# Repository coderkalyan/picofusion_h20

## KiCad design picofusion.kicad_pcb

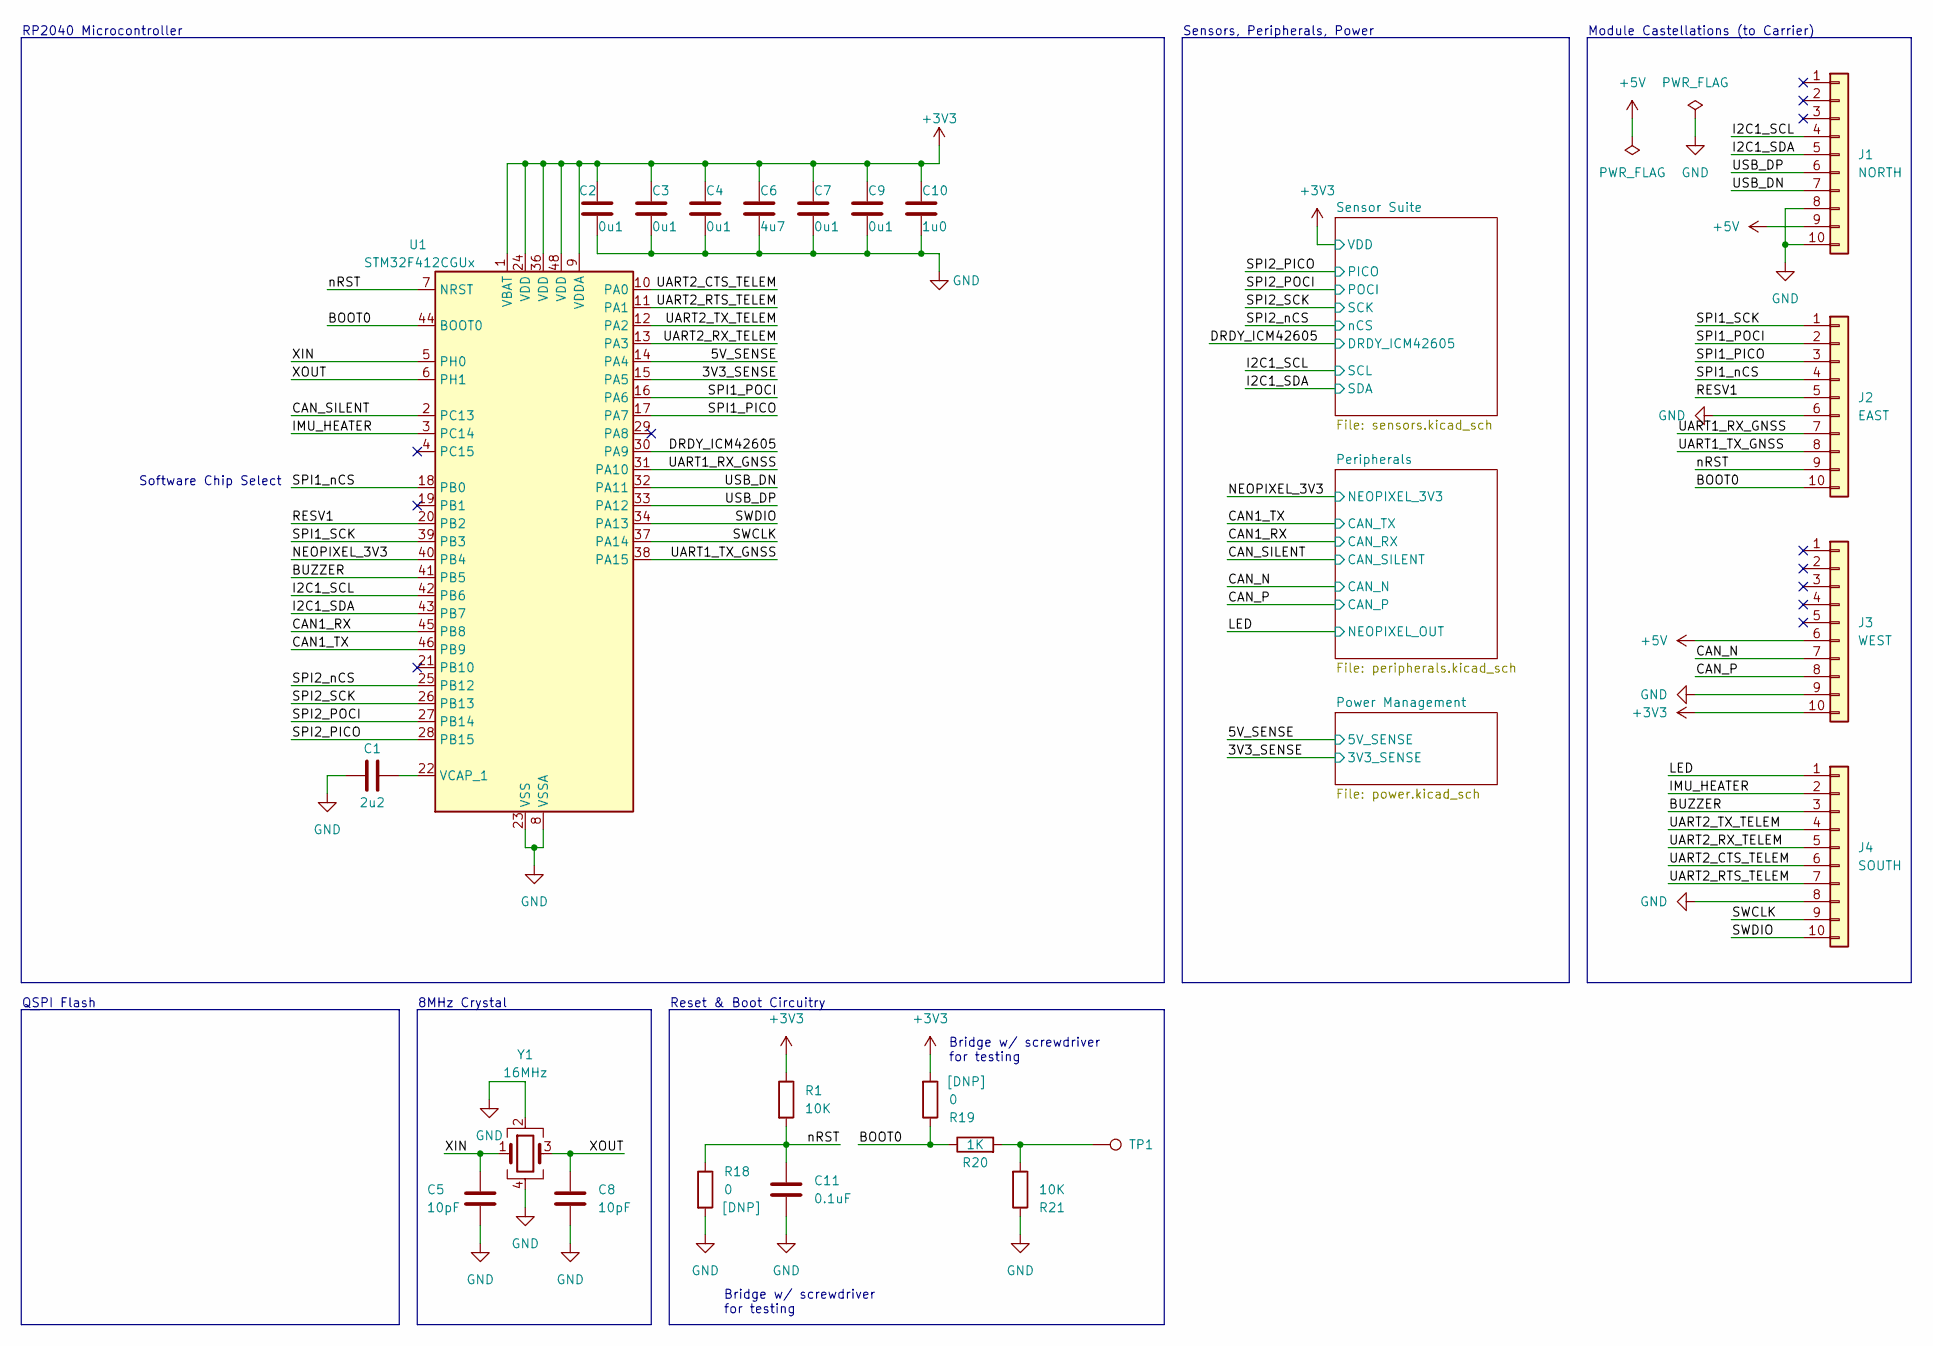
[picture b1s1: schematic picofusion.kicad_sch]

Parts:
C1: 2u2; C_0201_0603Metric
C2, C3, C4, C7, C9: 0u1; C_0201_0603Metric
C5, C8: 10pF; C_0402_1005Metric
C6: 4u7; C_0201_0603Metric
C10: 1u0; C_0201_0603Metric
C11: 0.1uF; C_0201_0603Metric
J1: NORTH; PinCastellation_1x10_P2.00mm_Vertical
J2: EAST; PinCastellation_1x10_P2.00mm_Vertical
J3: WEST; PinCastellation_1x10_P2.00mm_Vertical
J4: SOUTH; PinCastellation_1x10_P2.00mm_Vertical
R1: 10K; R_0201_0603Metric
R18, R19: 0; TestPoint_2Pin_0402_1005Metric
R20: 1K; R_0201_0603Metric
R21: 10K; R_0402_1005Metric
TP1: TestPoint; TestPoint_Pad_1.0x1.0mm
U1: STM32F412CGUx; QFN-48-1EP_7x7mm_P0.5mm_EP5.6x5.6mm
Y1: 16MHz; Crystal_SMD_2016-4Pin_2.0x1.6mm; Part R2520-12.000-10-3030-TR

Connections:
+3V3: C2.1, C3.1, C4.1, C6.1, C7.1, C9.1, C10.1, J3.10, R1.1, R19.2, U1.1 (VBAT), U1.9 (VDDA), U1.24 (VDD), U1.36 (VDD), U1.48 (VDD); also elsewhere on the board
+5V: J1.9, J3.6; also elsewhere on the board
/3V3_SENSE: U1.15 (PA5); also elsewhere on the board
/5V_SENSE: U1.14 (PA4); also elsewhere on the board
/BOOT0: J2.10, R19.1, R20.1, U1.44 (BOOT0)
/BUZZER: J4.3, U1.41 (PB5)
/CAN1_RX: U1.45 (PB8); also elsewhere on the board
/CAN1_TX: U1.46 (PB9); also elsewhere on the board
/CAN_N: J3.7; also elsewhere on the board
/CAN_P: J3.8; also elsewhere on the board
/CAN_SILENT: U1.2 (PC13); also elsewhere on the board
/DRDY_ICM42605: U1.30 (PA9); also elsewhere on the board
/I2C1_SCL: J1.4, U1.42 (PB6); also elsewhere on the board
/I2C1_SDA: J1.5, U1.43 (PB7); also elsewhere on the board
/IMU_HEATER: J4.2, U1.3 (PC14)
/LED: J4.1; also elsewhere on the board
/NEOPIXEL_3V3: U1.40 (PB4); also elsewhere on the board
/RESV1: J2.5, U1.20 (PB2)
/SPI1_PICO: J2.3, U1.17 (PA7)
/SPI1_POCI: J2.2, U1.16 (PA6)
/SPI1_SCK: J2.1, U1.39 (PB3)
/SPI1_nCS: J2.4, U1.18 (PB0)
/SPI2_PICO: U1.28 (PB15); also elsewhere on the board
/SPI2_POCI: U1.27 (PB14); also elsewhere on the board
/SPI2_SCK: U1.26 (PB13); also elsewhere on the board
/SPI2_nCS: U1.25 (PB12); also elsewhere on the board
/SWCLK: J4.9, U1.37 (PA14)
/SWDIO: J4.10, U1.34 (PA13)
/UART1_RX_GNSS: J2.7, U1.31 (PA10)
/UART1_TX_GNSS: J2.8, U1.38 (PA15)
/UART2_CTS_TELEM: J4.6, U1.10 (PA0)
/UART2_RTS_TELEM: J4.7, U1.11 (PA1)
/UART2_RX_TELEM: J4.5, U1.13 (PA3)
/UART2_TX_TELEM: J4.4, U1.12 (PA2)
/USB_DN: J1.7, U1.32 (PA11)
/USB_DP: J1.6, U1.33 (PA12)
/XIN: C5.1, U1.5 (PH0), Y1.1
/XOUT: C8.1, U1.6 (PH1), Y1.3
/nRST: C11.1, J2.9, R1.2, R18.1, U1.7 (NRST)
unnamed: R20.2, R21.2, TP1.1
unnamed: C1.2, U1.22 (VCAP_1)

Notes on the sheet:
Bridge w/ screwdriver for testing
RP2040 Microcontroller
Software Chip Select
QSPI Flash
8MHz Crystal
Module Castellations (to Carrier)
Sensors, Peripherals, Power
Reset & Boot Circuitry

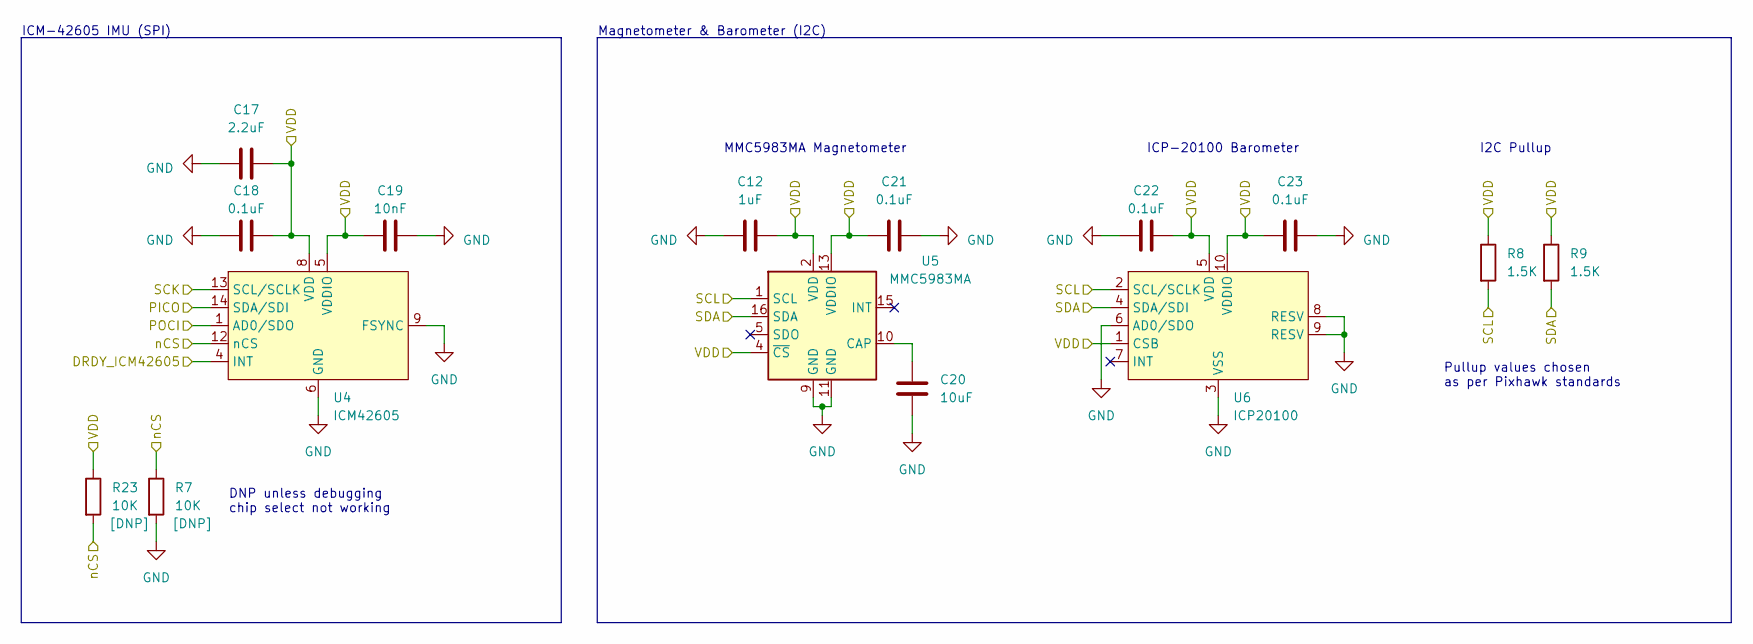
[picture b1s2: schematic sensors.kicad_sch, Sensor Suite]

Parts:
C12: 1uF; C_0201_0603Metric
C17: 2.2uF; C_0201_0603Metric
C18, C21, C22, C23: 0.1uF; C_0201_0603Metric
C19: 10nF; C_0201_0603Metric
C20: 10uF; C_0402_1005Metric
R7, R23: 10K; R_0201_0603Metric
R8, R9: 1.5K; R_0201_0603Metric
U4: ICM42605; LGA-14_3x2.5mm_P0.5mm_LayoutBorder3x4y
U5: MMC5983MA; LGA-16_3x3mm_P0.5mm
U6: ICP20100; PQFN50P200X200X85-10N

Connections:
+3V3: C12.2, C17.2, C18.2, C19.1, C21.1, C22.2, C23.1, R8.1, R9.1, R23.1, U4.5 (VDDIO), U4.8 (VDD), U5.2 (VDD), U5.4 (~CS), U5.13 (VDDIO), U6.1 (CSB), U6.5 (VDD), U6.10 (VDDIO); also elsewhere on the board
/DRDY_ICM42605: U4.4 (INT); also elsewhere on the board
/I2C1_SCL: R8.2, U5.1 (SCL), U6.2 (SCL/SCLK); also elsewhere on the board
/I2C1_SDA: R9.2, U5.16 (SDA), U6.4 (SDA/SDI); also elsewhere on the board
/SPI2_PICO: U4.14 (SDA/SDI); also elsewhere on the board
/SPI2_POCI: U4.1 (AD0/SDO); also elsewhere on the board
/SPI2_SCK: U4.13 (SCL/SCLK); also elsewhere on the board
/SPI2_nCS: R7.1, R23.2, U4.12 (nCS); also elsewhere on the board
unnamed: C20.1, U5.10 (CAP)

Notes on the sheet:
ICM-42605 IMU (SPI)
DNP unless debugging chip select not working
Magnetometer & Barometer (I2C)
ICP-20100 Barometer
I2C Pullup
Pullup values chosen as per Pixhawk standards
MMC5983MA Magnetometer

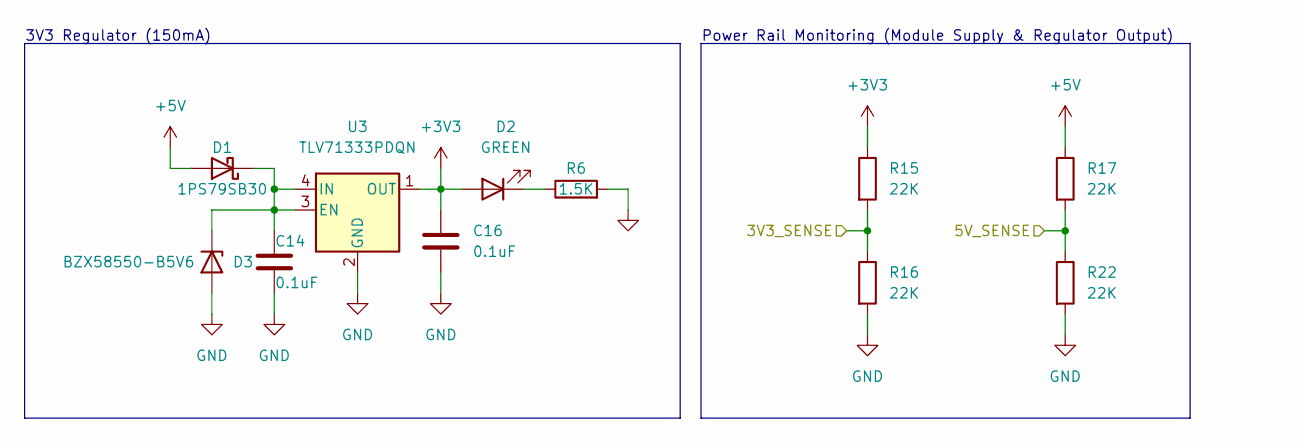
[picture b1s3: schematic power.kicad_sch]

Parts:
C14, C16: 0.1uF; C_0603_1608Metric
D1: 1PS79SB30; D_SOD-523
D2: GREEN; LED_0402_1005Metric; Part QBLP595-IG
D3: BZX58550-B5V6; D_SOD-523
R6: 1.5K; R_0402_1005Metric
R15, R16, R17, R22: 22K; R_0201_0603Metric
U3: TLV71333PDQN; Texas_X2SON-4_1x1mm_P0.65mm

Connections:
+3V3: C16.1, D2.2 (A), R15.1, U3.1 (OUT); also elsewhere on the board
+5V: D1.2 (A), R17.1; also elsewhere on the board
/3V3_SENSE: R15.2, R16.1; also elsewhere on the board
/5V_SENSE: R17.2, R22.1; also elsewhere on the board
unnamed: C14.1, D1.1 (K), D3.1 (K), U3.3 (EN), U3.4 (IN)
unnamed: D2.1 (K), R6.1

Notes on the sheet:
Power Rail Monitoring (Module Supply & Regulator Output)
3V3 Regulator (150mA)

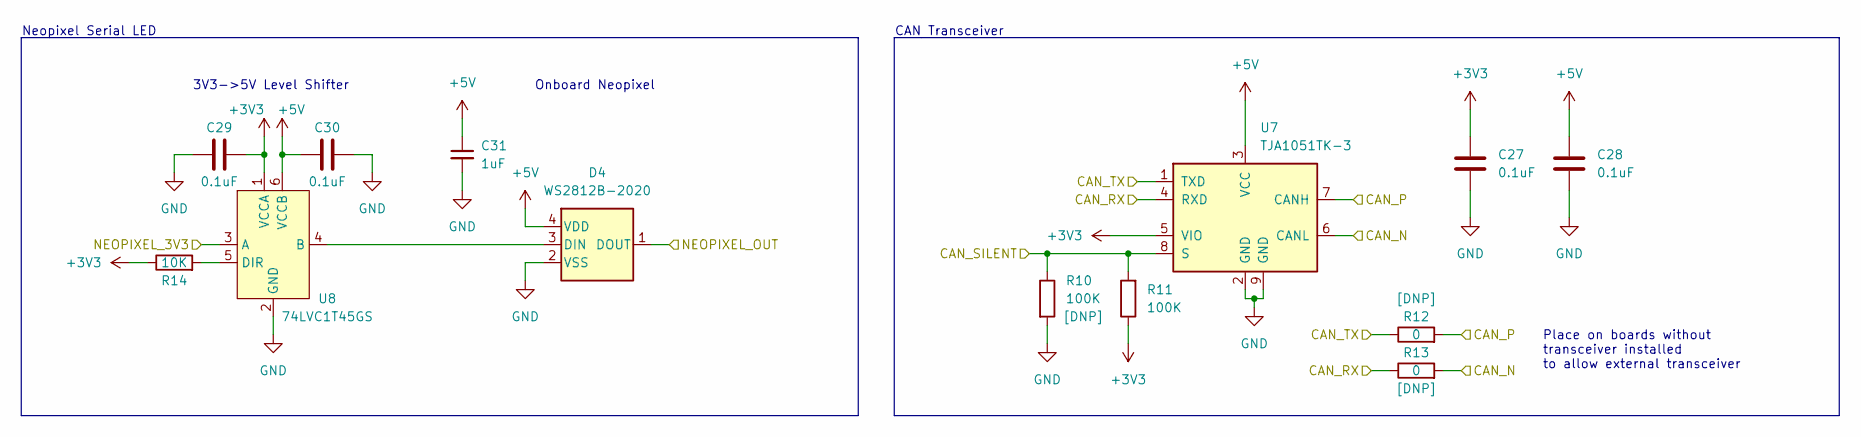
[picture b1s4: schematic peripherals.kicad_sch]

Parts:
C27, C28, C29, C30: 0.1uF; C_0201_0603Metric
C31: 1uF; C_0201_0603Metric
D4: WS2812B-2020
R10, R11: 100K; R_0402_1005Metric
R12, R13: 0; R_0402_1005Metric
R14: 10K; R_0402_1005Metric
U7: TJA1051TK-3; DFN-8-1EP_3x3mm_P0.65mm_EP1.55x2.4mm
U8: 74LVC1T45GS; PSON35P100X100X35-6N

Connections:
+3V3: C27.1, C29.2, R11.1, R14.1, U7.5 (VIO), U8.1 (VCCA); also elsewhere on the board
+5V: C28.1, C30.2, C31.1, D4.4 (VDD), U7.3 (VCC), U8.6 (VCCB); also elsewhere on the board
/CAN1_RX: R13.1, U7.4 (RXD); also elsewhere on the board
/CAN1_TX: R12.1, U7.1 (TXD); also elsewhere on the board
/CAN_N: R13.2, U7.6 (CANL); also elsewhere on the board
/CAN_P: R12.2, U7.7 (CANH); also elsewhere on the board
/CAN_SILENT: R10.1, R11.2, U7.8 (S); also elsewhere on the board
/LED: D4.1 (DOUT); also elsewhere on the board
/NEOPIXEL_3V3: U8.3 (A); also elsewhere on the board
unnamed: D4.3 (DIN), U8.4 (B)
unnamed: R14.2, U8.5 (DIR)

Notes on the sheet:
3V3->5V Level Shifter
Onboard Neopixel
Neopixel Serial LED
Place on boards without transceiver installed to allow external transceiver
CAN Transceiver

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
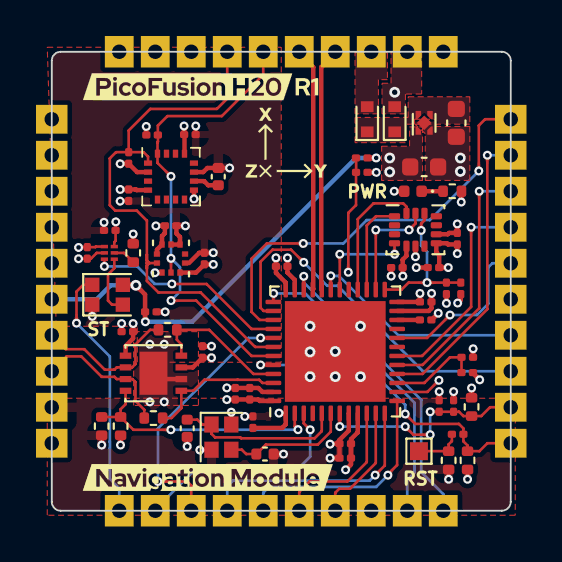
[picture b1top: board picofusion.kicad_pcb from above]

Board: 4 copper layers, 25.5 x 25.5 mm, 62 parts (0 on the bottom side), 47 nets.

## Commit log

2023-03-08 draft: schematic and layout for H20R1
2023-04-05 h20r1: more updates
2023-04-07 replace sdio with spi2, finish routing, front silkscreen
2023-04-09 cleanup and review of PicoFusion H20 R1
    * update to KiCad 7
    * add thermal vias to STM32F412CG QFN footprint
    * update silkscreen branding
    * update applicable silkscreen to Kicad 7 native text
    * fix UART GNSS TX/RX swapped
    * minor routing changes and cleanup
2023-04-09 routing: add teardrops
2023-04-10 update standard libs
2023-04-20 update usb impedance/trace width, silkscreen
2023-04-21 update crystal
2023-04-21 add step file
2023-08-30 gitignore: add python env
